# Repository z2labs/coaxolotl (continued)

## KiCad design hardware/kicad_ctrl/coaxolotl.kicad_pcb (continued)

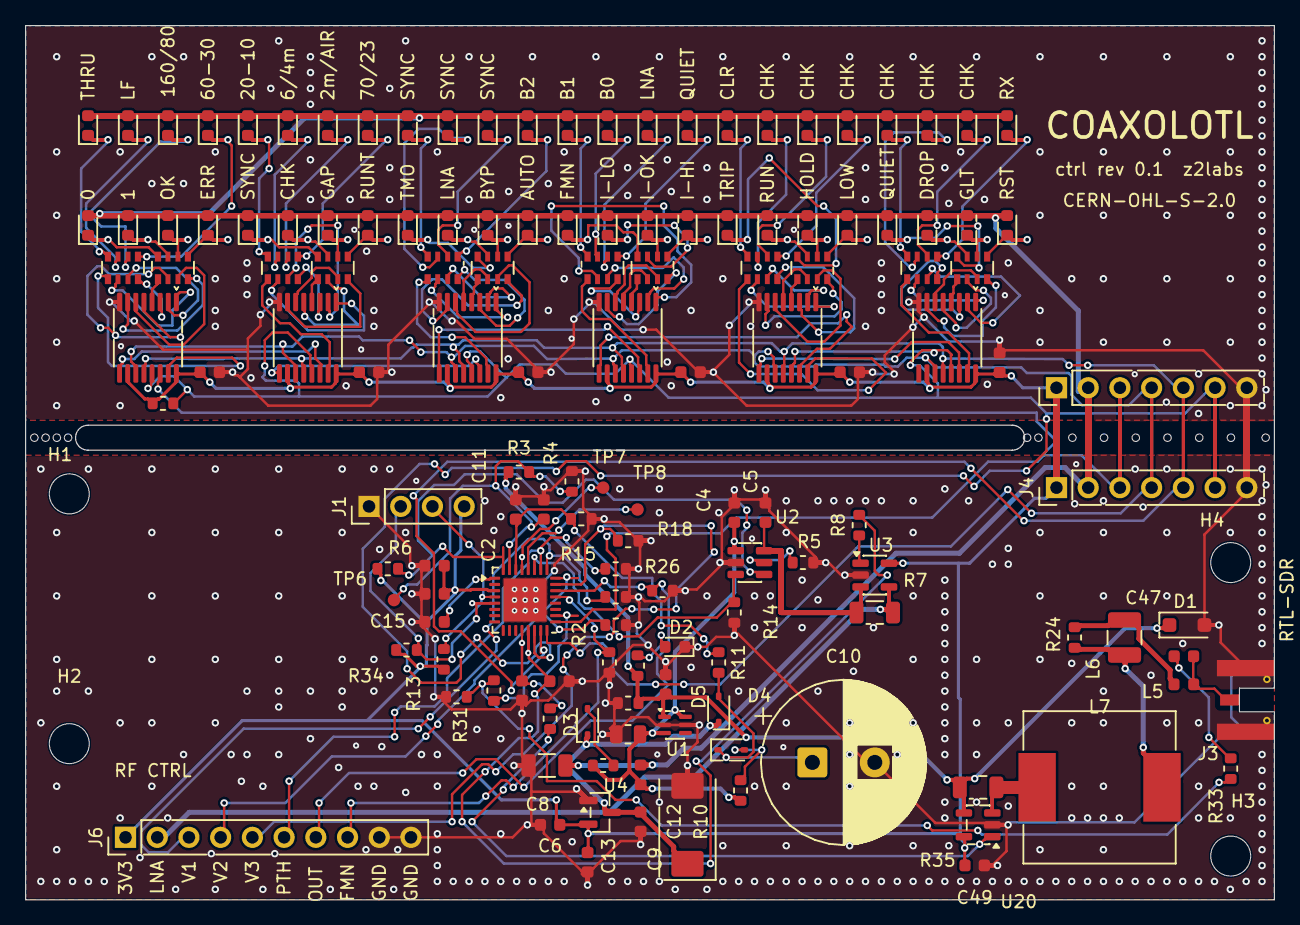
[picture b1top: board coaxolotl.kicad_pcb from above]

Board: 2 copper layers, 100.0 x 70.0 mm, 159 parts (0 on the bottom side), 144 nets.

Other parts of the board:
H1, H2, H3, H4: MountingHole_3.2mm_M3
MB1, MB2, MB3, MB4, MB5, MB6, MB7, MB8, MB9, MB10, MB11, MB12, MB13: MouseBite_NPTH_0.6mm

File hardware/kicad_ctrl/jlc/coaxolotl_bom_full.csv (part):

Qty,Comment,Designator,Footprint,LCSC Part #,MPN,Manufacturer,Basic/Extended,SMT/THT,Key spec,Checked at,Notes
14,100nF/16V/10%,"C1,C6,C7,C11,C15,C41,C42,C43,C44,C45,C46,C48,C49,C50",C_0603_1608Metric,C14663,CC0603KRX7R9BB104,YAGEO,Basic,SMT,100nF 50V X7R 10%,https://jlcpcb.com/partdetail/CC0603KRX7R9BB104/C14663,"LCSC stock only 1,100 (JLC stock may differ; 15 per board); C1591 CL10B104KB8NNNC is Extended and out of stock; checked 2026-10-27"
1,10nF/50V/10%,C2,C_0603_1608Metric,C57112,0603B103K500NT,FH (Fenghua),Basic,SMT,10nF 50V X7R 10%,https://jlcpcb.com/partdetail/0603B103K500NT/C57112,stock not shown; checked 2026-10-27
1,10uF/10V/20%,C3,C_0805_2012Metric,C15850,CL21A106KAYNNNE,Samsung,Basic,SMT,10uF 25V X5R 10%,https://jlcpcb.com/partdetail/CL21A106KAYNNNE/C15850,"LCSC stock 2,232,500; checked 2026-10-27"
5,1uF/16V/10%,"C4,C5,C12,C13,C14",C_0603_1608Metric,C15849,CL10A105KB8NNNC,Samsung,Basic,SMT,1uF 50V X5R 10%,https://jlcpcb.com/partdetail/CL10A105KB8NNNC/C15849,"LCSC stock 673,250; checked 2026-10-27"
1,47uF/10V/20%,C8,C_1206_3216Metric,C96123,CL31A476MPHNNNE,Samsung,Basic,SMT,47uF 10V X5R 20%,https://jlcpcb.com/partdetail/C96123,"LCSC stock 181,755; checked 2026-10-27"
1,330uF/6.3V/20%,C9,CP_EIA-7343-31_Kemet-D,C116745,T520D337M006ATE025,KEMET,Extended (JLC page not reached),SMT,330uF 6.3V polymer tantalum ESR 25mR,https://www.lcsc.com/product-detail/Tantalum-Capacitors_KEME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,"exact MPN; LCSC stock 1,716; checked 2026-10-27"
1,100pF/50V/C0G,C47,C_0603_1608Metric,C14858,CL10C101JB8NNNC,Samsung,Basic,SMT,100pF 50V C0G 5%,https://jlcpcb.com/partdetail/C14858,"LCSC stock 1,410,850; checked 2026-10-27"
1,SMF5.0A(SOD123F),D1,D_SOD-123F,C151296,SMF5.0A,Littelfuse,Extended,SMT,TVS 5V uni 200W,https://jlcpcb.com/partdetail/Littelfuse-SMF50A/C151296,SOD-123FL vs D_SOD-123F footprint - check land pattern; stock not shown; checked 2026-10-27
1,LED/GREEN(0603),D2,LED_0603_1608Metric,C12624,KT-0603G,Hubei KENTO,Extended,SMT,emerald green 513-528nm,https://jlcpcb.com/partdetail/Hubei_KENTOElec-KT0603G/C12624,"same LED as GREEN(0603); LCSC stock 428,600; checked 2026-10-27"
3,BAT54WS(SOD323),"D3,D4,D5",D_SOD-323,C304155,BAT54WS_R1_00001,PANJIT,unknown,SMT,Schottky 30V 200mA,https://www.lcsc.com/product-detail/C304155.html,"LCSC stock 7,340; CJ BAT54WS C22629 out of stock; checked 2026-10-27"
25,AMBER(0603),"D7,D8,D9,D10,D11,D12,D13,D14,D15,D16,D17,D18,D19,D20,D21,D22,D23,D24,D25,D26,D27,D28,D29,D30,D43",LED_0603_1608Metric,C965800,XL-1608UOC-06,XINGLIGHT,Extended,SMT,orange 600-610nm,https://jlcpcb.com/partdetail/Xinglight-XL_1608UOC06/C965800,"no Basic amber/orange 0603 found; orange 605nm used as amber; LCSC stock 359,800; checked 2026-10-27"
7,YELLOW(0603),"D31,D32,D41,D42,D44,D51,D53",LED_0603_1608Metric,C2287,KT-0603Y,Hubei KENTO,Extended,SMT,yellow 584-594nm,https://jlcpcb.com/partdetail/C2287,"LCSC stock 124,400; Everlight C72038 out of stock; alt XINGLIGHT XL-1608UYC-06 C965802 (1,220,400); checked 2026-10-27"
5,GREEN(0603),"D33,D40,D45,D48,D49",LED_0603_1608Metric,C12624,KT-0603G,Hubei KENTO,Extended,SMT,emerald green 513-528nm,https://jlcpcb.com/partdetail/Hubei_KENTOElec-KT0603G/C12624,"LCSC stock 428,600; Everlight C72043 green has 0 stock; checked 2026-10-27"
11,RED(0603),"D34,D35,D36,D37,D38,D39,D46,D47,D50,D52,D54",LED_0603_1608Metric,C2286,KT-0603R,Hubei KENTO,Basic,SMT,red 615-630nm,https://jlcpcb.com/partdetail/Hubei_KENTOElec-KT0603R/C2286,"LCSC stock 5,180,700; checked 2026-10-27"
1,FB0603/600R/1.3A,FB1,L_0603_1608Metric,C85833,BLM18KG601SN1D,Murata,Extended,SMT,600R@100MHz 1.3A 150mR,https://jlcpcb.com/partdetail/C85833,"exact MPN; LCSC stock 185,050; checked 2026-10-27"
1,SMA/EDGE(RTL-SDR),J3,SMA_EdgeLaunch_BWSMA-KE-P001_Air,C496550,BWSMA-KE-P001,BAT WIRELESS,Extended,SMT (edge mount),SMA jack 50R 18GHz for 1.57mm PCB,https://jlcpcb.com/partdetail/C496550,"replaces Amphenol 132289 C3172723 (JLC stock 0); JLC stock 73,770; bottom legs hand-soldered; checked 2026-10-28"
1,100nH/1A(0603),L5,L_0603_1608Metric,C1858173,LQW18CNR10K0ZD,Murata,Extended,SMT,100nH 10% wirewound 1A DCR 0.1R SRF>=1260MHz,https://www.lcsc.com/product-detail/C1858173.html,LCSC 4243 in stock; checked 2026-11-07
1,10uH/0.45A(1210),L6,L_1210_3225Metric,C86069,LQH32CN100K33L,Murata,Extended,SMT,10uH 10% 450mA 0.39ohm wire-wound,https://lcsc.com/product-detail/Inductors-SMD_muRata_LQH32CN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,"LCSC stock 3,725; L6 carries the coax DC (~150 mA); chosen by Zoltan 2026-10-27; checked 2026-10-27"
1,470uH/1A,L7,L_YJYCOIN_YPRH1209,C718309,YPRH1209-471M,YJYCOIN,Extended,SMT,470uH 20% 1.06A DCR 0.471R shielded,https://www.lcsc.com/product-detail/Power-Inductors_YJYCOIN-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,LCSC 1469 in stock; checked 2026-11-07
1,680R/1%,R1,R_0603_1608Metric,C23228,0603WAF6800T5E,UNI-ROYAL,Basic,SMT,680R 1% 100mW,https://jlcpcb.com/partdetail/C23228,stock not shown; checked 2026-10-27
1,3k3/5%,R2,R_0603_1608Metric,C22978,0603WAF3301T5E,UNI-ROYAL,Basic,SMT,3.3k 1% 100mW,https://jlcpcb.com/partdetail/0603WAF3301T5E/C22978,stock not shown; checked 2026-10-27
1,11k/1%,R3,R_0603_1608Metric,C25950,0603WAF1102T5E,UNI-ROYAL,Basic,SMT,11k 1% 100mW,https://lcsc.com/product-detail/Chip-Resistor-Surface-Mount_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,LCSC 113200 in stock; checked 2026-11-07
1,22k/1%,R4,R_0603_1608Metric,C31850,0603WAF2202T5E,UNI-ROYAL,Basic,SMT,22k 1% 100mW,https://jlcpcb.com/partdetail/C31850,stock not shown; checked 2026-10-27
1,150k/1%,R5,R_0603_1608Metric,C22807,0603WAF1503T5E,UNI-ROYAL,Basic,SMT,150k 1% 100mW,https://jlcpcb.com/partdetail/C22807,stock not shown; checked 2026-10-27
1,100k/5%,R6,R_0603_1608Metric,C25803,0603WAF1003T5E,UNI-ROYAL,Basic,SMT,100k 1% 100mW,https://jlcpcb.com/partdetail/0603WAF1003T5E/C25803,stock not shown; checked 2026-10-27
1,0R39/1%/0.25W,R7,R_1206_3216Metric,C25339,1206W4F390LT5E,UNI-ROYAL(Uniroyal Elec),Extended,SMT,390mR 1% 250mW thick film,https://jlcpcb.com/partdetail/C25339,RS-06MR390FT C343953 had 13 in stock; Uniroyal 1206 14296 in stock; checked 2026-10-29
3,1k/1%,"R8,R33,R36",R_0603_1608Metric,C21190,0603WAF1001T5E,UNI-ROYAL,Basic,SMT,1k 1% 100mW,https://jlcpcb.com/partdetail/0603WAF1001T5E/C21190,stock not shown; checked 2026-10-27
1,100R/5%,R9,R_0603_1608Metric,C22775,0603WAF1000T5E,UNI-ROYAL,Basic,SMT,100R 1% 100mW,https://jlcpcb.com/partdetail/0603WAF1000T5E/C22775,"LCSC stock 2,781,900; checked 2026-10-27"
2,220R/5%,"R10,R24",R_0603_1608Metric,C22962,0603WAF2200T5E,UNI-ROYAL,Basic,SMT,220R 1% 100mW,https://jlcpcb.com/partdetail/0603WAF2200T5E/C22962,stock not shown; checked 2026-10-27
2,1M/1%,"R11,R12",R_0603_1608Metric,C22935,0603WAF1004T5E,UNI-ROYAL,Basic,SMT,1M 1% 100mW,https://jlcpcb.com/partdetail/0603WAF1004T5E/C22935,stock not shown; checked 2026-10-27
10,10k/5%,"R13,R14,R15,R16,R17,R18,R19,R20,R26,R34",R_0603_1608Metric,C25804,0603WAF1002T5E,UNI-ROYAL,Basic,SMT,10k 1% 100mW,https://jlcpcb.com/partdetail/0603WAF1002T5E/C25804,1% part for 5% line; stock not shown; checked 2026-10-27
1,4k7/1%,R31,R_0603_1608Metric,C23162,0603WAF4701T5E,UNI-ROYAL,Basic,SMT,4.7k 1% 100mW,https://jlcpcb.com/partdetail/23889-0603WAF4701T5E/C23162,back-channel tap R_BCN1; stock 14.8M; checked 2026-11-02
1,51R/1%,R32,R_0603_1608Metric,C23197,0603WAF510JT5E,UNI-ROYAL,Basic,SMT,51R 1% 100mW,https://jlcpcb.com/partdetail/23924-0603WAF510JT5E/C23197,back-channel tap R_BCN2; stock 2.1M; checked 2026-11-02
1,0R1/1%/0.25W,R35,R_1206_3216Metric,C25334,1206W4F100LT5E,UNI-ROYAL(Uniroyal Elec),Basic,SMT,100mR 1% 250mW thick film,https://www.lcsc.com/product-detail/C25334.html,coax current shunt; JLC stock 662259 (basic) checked 2026-11-07
12,2k2x4/5%(CAY16),"RN1,RN2,RN3,RN4,RN5,RN6,RN7,RN8,RN9,RN10,RN11,RN12",R_Array_Convex_4x0603,C12001,4D03WGJ0222T5E,UNI-ROYAL,Extended,SMT,4x2.2k 5% 1/16W 8-pin array,https://jlcpcb.com/partdetail/4D03WGJ0222T5E/C12001,"CAY16-222J4LF not on LCSC; LCSC stock 17,040; JLC page does not state convex/concave - check 4D03 drawing against R_Array_Convex_4x0603 (Bourns CAY16 is convex); checked 2026-10-27"
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
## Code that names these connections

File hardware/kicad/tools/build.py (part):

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VARIANT = os.environ.get("COAX_VARIANT", "")
CTRL = VARIANT == "ctrl"
OUT = pathlib.Path(__file__).resolve().parent.parent.parent / ("kicad_ctrl" if CTRL else "kicad")
# COAX_MCU=bb52: EFM8BB52F32 (QFN32) with its own BEACON pin and the back-channel tap; the control board default.
# bb21: EFM8BB21F16G (QFN20), the RF board as routed.
MCU = os.environ.get("COAX_MCU", "bb52" if CTRL else "bb21")
PROJECT = "coaxolotl"
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    s.add(R("R3", "11k/1%", 111.76, 55.88, "VCOAX", "SENSE"))
    s.add(R("R4", "22k/1%", 111.76, 68.58, "SENSE", "GND"))
    s.zone = "POWER"
    s.rail_pin("D1", "1", "VCOAX")
    s.w((33.02, 50.8), (22.86, 50.8))
    s.flag(22.86, 50.8, "VCOAX")
    s.gnd("D1", "2")
    for ref in ("C1", "R1"):
        s.rail_pin(ref, "1", "VCOAX")
        s.gnd(ref, "2")
    s.rail_pin("R2", "1", "VCOAX")
    s.w(s.pt("R2", "2"), s.pt("D2", "2"))
    s.gnd("D2", "1")
    s.rail_pin("R3", "1", "VCOAX")
    s.w(s.pt("R3", "2"), s.pt("R4", "1"))
    s.gnd("R4", "2")
    s.w((111.76, 62.23), (124.46, 62.23))
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               {"1": "VCOAX", "4": None, "6": "VMAIN", "3": "VMAIN", "2": "GND", "5": "GND"},
               txt=(153.67, 50.8)))
    s.add(C("C3", "10uF/10V/20%", 180.34, 62.23, "VMAIN", "GND", fp=C0805, Place="U1.6"))
    s.rail_pin("U1", "1", "VCOAX")
    s.nc("U1", "4")
    s.w(s.pt("U1", "6"), (187.96, 58.42), (187.96, 55.88))
    s.rail("VMAIN", 187.96, 55.88)
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    s.rail("VMAIN", 223.52, 53.34)
    s.gnd("C4", "2")
    s.pw("U2", "3", (226.06, None), (None, 71.12), (210.82, None))
    s.hlabel("LNA_EN", 210.82, 71.12, "L", "input")
    s.gnd("R14", "2")
    s.pw("U2", "5", (251.46, None), (None, 60.96))
    s.gnd("R5", "2")
    s.pw("U2", "4", (None, 96.52), (325.12, None))
    s.hlabel("FAULT_N", 325.12, 96.52, "R", "output")
    s.gnd("U2", "2")
    s.w(s.pt("U2", "6"), s.pt("R7", "1"))
    s.gnd("C5", "2")
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    s.gnd("C6", "2")
    s.gnd("U3", "2")
    s.pw("U3", "1", (325.12, None))
    s.hlabel("ILNA", 325.12, 78.74, "R", "output")
    s.intent("Ilim = f(R5), TPS2553 Eq.1: VERIFY IOS(min) > 130 mA", 203.2, 101.6)
    s.intent("ILNA = 0.39R x 50 V/V = 19.5 mV/mA (100 mA -> 1.95 V); Kelvin taps at R7 pads", 203.2, 104.78)

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    s.w(s.pt("R11", "2"), s.pt("R12", "1"))
    s.gnd("R12", "2")
    s.w((60.96, 162.56), (43.18, 162.56))
    s.hlabel("SCAP_ADC", 43.18, 162.56, "L", "output")
    s.intent("fast path R9/D3: VHOLD up in ~30 ms (100R x 330uF) -> MCU boots", 17.78, 184.15)
    s.intent("slow path R10/D4: tau ~22 s (220R x 0.1F); ride-through ~4 min at 0.6 mA", 17.78, 187.33)
    s.intent("SCAP_ADC = VSCAP / 2 (HOLD lamp at >= 3.6 V)", 17.78, 190.5)
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

def sheet_mcu_bb52(lib) -> DSheet:
    """EFM8BB52F32 QFN32 (firmware/src/hal_efm8bb52.c): own BEACON pin P1.7, UART0 test points for the factory
    bootloader, C2D no longer shared, 10 spare pins (driven low by the firmware, not connected here)."""
    s = sheet(lib, "MCU", "mcu.kicad_sch", "EFM8BB52F32 (QFN32), C2 debug, UART test points, ADC input conditioning")
    s.zone = "DIGITAL"
    s.frame(76.2, 53.34, 167.64, 142.24, "MCU")
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    s.rail_pin("R13", "1", "+3V3")
    s.w(s.pt("R13", "2"), (139.7, 83.82))
    s.rail_pin("R34", "1", "+3V3")
    s.label("C2D", *s.pt("R34", "2"), 180)
    s.label("C2D", *s.pt("U5", "5"), 180)
    s.add(Part("TP7", "Connector:TestPoint", "TP/TX", 111.76, 96.52, 0, TP, {"1": "TP_TX"}, dnp=True))
    s.add(Part("TP8", "Connector:TestPoint", "TP/RX", 111.76, 104.14, 0, TP, {"1": "TP_RX"}, dnp=True))
    s.label("TP_TX", *s.pt("TP7", "1"), 180)
    s.label("TP_RX", *s.pt("TP8", "1"), 180)
    s.add(R("R6", "100k/5%", 129.54, 99.06, "+3V3", "FAULT_N", Place="U5.32"))
    s.pw("U5", "32", (99.06, None))
    s.hlabel("FAULT_N", 99.06, s.pt("U5", "32")[1], "L", "input")
    s.rail_pin("R6", "1", "+3V3")
    s.w(s.pt("R6", "2"), (129.54, s.pt("U5", "32")[1]))
    s.pw("U5", "28", (144.78, None))
    s.label("TP_RX", 144.78, s.pt("U5", "28")[1], 180)
    s.zone = "ANALOG"
    s.add(R("R8", "1k/1%", 124.46, s.pt("U5", "13")[1], "ILNA", "ILNA_ADC", rot=90, Place="U5.13"))
    s.add(C("C7", "100nF/16V/10%", 137.16, s.pt("U5", "13")[1] + 3.81, "ILNA_ADC", "GND", Place="U5.13"))
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    s.zone = "DIGITAL"
    s.w(s.pt("R8", "2"), s.pt("U5", "13"))
    s.pw("R8", "1", (99.06, None))
    s.hlabel("ILNA", 99.06, s.pt("U5", "13")[1], "L", "input")
    s.gnd("C7", "2")
    s.pw("U5", "30", (99.06, None))
    s.hlabel("SCAP_ADC", 99.06, s.pt("U5", "30")[1], "L", "input")
    s.gnd("C11", "2")
    s.w(s.pt("U5", "1"), s.pt("C50", "2"))
    s.gnd("C50", "1")
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    s.w(s.pt("U5", "12"), s.pt("R36", "2"))
    s.gnd("C48", "2")
    s.pw("R36", "1", (215.9, None))
    s.hlabel("ITOT", 215.9, s.pt("U5", "12")[1], "R", "input")
    for num, net in [("27", "LNA_EN"), ("26", "LNA_PATH"), ("25", "SW_V1"), ("24", "SW_V2"), ("23", "SW_V3"),
                     ("22", "LNA_PATH_OUT"), ("21", "FMN"), ("17", "LED_SER"), ("16", "LED_SCK"),
                     ("15", "LED_RCK"), ("14", "LED_OE_N"), ("18", "BEACON")]:
        end = s.pw("U5", num, (215.9, None))
        s.hlabel(net, *end, "R", "output")
    end = s.pw("U5", "29", (200.66, None))
    s.label("TP_TX", *end)
    for num in ("10", "9", "8", "7", "6", "20", "19", "11", "2"):
        s.nc("U5", num)
    s.intent("J1: 1=GND 2=C2D 3=C2CK 4=3V3. TP7/TP8: UART0 for the factory bootloader (C2D low at reset).",
             86.36, 73.66)
    s.intent("QFN32: own BEACON pin (P1.7 = PCA CEX0 during a reply), C2D not shared, 9 spares driven low.",
             78.74, 184.15)
    s.intent("P0.0 = VREF (precision 2.4 V, C50). SENSE = P0.2, digital and ADC at once (PRTDRV.COEX).",
             78.74, 193.67)
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    s = sheet(lib, "MCU", "mcu.kicad_sch", "EFM8BB21F16G (QFN20), C2 debug, ADC input conditioning")
    s.zone = "DIGITAL"
    s.frame(76.2, 53.34, 167.64, 142.24, "MCU")
    # QFN20: 16 port pins, all used. FMN shares P2.0 with C2D (through R30: the debugger overrides it).
    s.add(Part("U5", "coaxolotl:EFM8BB21F16G-C-QFN20", "EFM8BB21F16G-C(QFN20)", 165.1, 127.0, 0,
               "coaxolotl:EFM8_QFN-20-1EP_3x3mm_P0.5mm_EP1.7x1.7mm",
               {"4": "+3V3", "3": "GND", "12": "GND", "21": "GND", "5": "RST_N", "6": "C2D", "17": "FAULT_N",
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    s.add(R("R13", "10k/5%", 139.7, 76.2, "+3V3", "RST_N", Place="U5.5"))
    s.w(s.pt("J1", "3"), s.pt("U5", "5"))
    s.w(s.pt("J1", "2"), s.pt("U5", "6"))
    s.label("C2D", *s.pt("U5", "6"), 180)
    s.rail_pin("J1", "4", "+3V3")
    s.gnd("J1", "1")
    s.rail_pin("R13", "1", "+3V3")
    s.w(s.pt("R13", "2"), (139.7, 83.82))
    s.add(R("R6", "100k/5%", 129.54, 99.06, "+3V3", "FAULT_N", Place="U5.17"))
    s.pw("U5", "17", (99.06, None))
    s.hlabel("FAULT_N", 99.06, 106.68, "L", "input")
    s.rail_pin("R6", "1", "+3V3")
    s.w(s.pt("R6", "2"), (129.54, 106.68))
    s.zone = "ANALOG"
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            Note="FMN shares P2.0 with C2D: the debugger overrides the line through this resistor"))
    s.w(s.pt("R8", "2"), s.pt("U5", "19"))
    s.pw("R8", "1", (99.06, None))
    s.hlabel("ILNA", 99.06, 121.92, "L", "input")
    s.gnd("C7", "2")
    s.pw("U5", "20", (99.06, None))
    s.hlabel("SCAP_ADC", 99.06, 137.16, "L", "input")
    s.gnd("C11", "2")
    s.pw("U5", "2", (142.24, None))
    s.pw("U5", "1", (142.24, None), (None, 152.4))
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        end = s.pw("U5", num, (215.9, None))
        s.hlabel(net, *end, "R", "output")
    s.w(s.pt("R30", "1"), (s.pt("R30", "1")[0] - 2.54, s.pt("R30", "1")[1]))
    s.label("C2D", s.pt("R30", "1")[0] - 2.54, s.pt("R30", "1")[1], 180)
    end = s.pw("R30", "2", (215.9, None))
    s.hlabel("FMN", *end, "R", "output")
    s.intent("J1: 1=GND 2=C2D 3=C2CK 4=3V3", 86.36, 73.66)
    s.intent("QFN20 (QSOP24 end of life): all 16 port pins used; the old TP_TX test point is gone,",
             78.74, 184.15)
    s.intent("LED_OE_N moved to P0.4, the lamp chain to P1.4-P1.6, FMN to P2.0/C2D through R30.",
             78.74, 187.33)
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    s.add(R("R22", "0R/0603", 226.06, yl, "FMN_IN", "FMN_OUT", rot=90, Note="fit when the notch is not fitted",
            txt=(226.06, yl - 6.35, None)))
    s.w(s.pt("U12", "3"), s.pt("R22", "1"))
    _pe42522(s, "U9", 231.14, yn, "FMN_IN", "FMN", "FMN_THRU", "FMN_TANK_A", value="NA(PE42520C-Z)",
             dnp=True, txt=(231.14, 177.8, None))
    _pe42522(s, "U10", 281.94, yn, "FMN_OUT", "FMN", "FMN_THRU", "FMN_TANK_B", inv=True, value="NA(PE42520C-Z)",
             dnp=True, mirror=True, txt=(281.94, 177.8, None))
    for ref in ("U9", "U10"):
        x, y = s.pt(ref, "16")
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    s.add(R("R19", "10k/5%", 203.2, yf + 3.81, "FMN", "GND", Note="notch out while MCU in reset"))
    s.w((35.56, yp), (86.36, yp))
    s.w((99.06, yp + 5.08), (398.78, yp + 5.08))
    s.hlabel("LNA_PATH_OUT", 99.06, yp + 5.08, "L", "input")
    s.add(R("R26", "10k/5%", 121.92, yp + 5.08 + 3.81, "LNA_PATH_OUT", "GND", Note="bypass while MCU in reset"))
    s.gnd("R26", "2")
    s.w((190.5, yf), (297.18, yf))
    s.hlabel("LNA_PATH", 35.56, yp, "L", "input")
    s.hlabel("FMN", 190.5, yf, "L", "input")
    s.gnd("R15", "2")
    s.gnd("R19", "2")
    s.intent("LNA_PATH (U6) and LNA_PATH_OUT (U7, own GPIO): 0 = bypass, 1 = LNA. FMN 0 = through. U7/U10: LS = GND.", 228.6, 206.38)
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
